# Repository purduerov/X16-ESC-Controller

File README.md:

# Readme for X16-ESC-Controller
This board turns signals from the Pi into PWM signals that go to the ESC Adapter

Whenever you make a new part, download the datasheet and save it here _**and**_ with the part in the parts library

Always pull other people's changes before beginning to work
`git pull`

Be sure to push your changes after  working on them. Run:
1. `git add .` to add any files in this directory or a subdirectory
or `git add -u` to add any modified files
2. (Optional) `git clean -nX` to see what ignored files can be removed
	`git clean -fX` removes ignored files (Eagle backups)
3. `git commit -m "helpful commit message"` with a description of the work that you did
4. `git push` to push your work to github

Other helpful commands
* `git status` says information about modified and staged files
* `git log` shows the recent commits of the repository
* `git log filename.extension` show the recent commits for just that file
* `git checkout first-couple-letter-of-commit-id` lets you go back to a previous version
* `git checkout master` brings you back to the latest commit
* `git tag` lists the tags
* `git tag -a orderX -m "the version of the board placed for the X'th order"` tag a specific commit
* `git push --tags` needed to push tags to remote
* `git show orderX` show the commit log for the given tag
* `git checkout orderX` go back and interact with the files at the tagged commit

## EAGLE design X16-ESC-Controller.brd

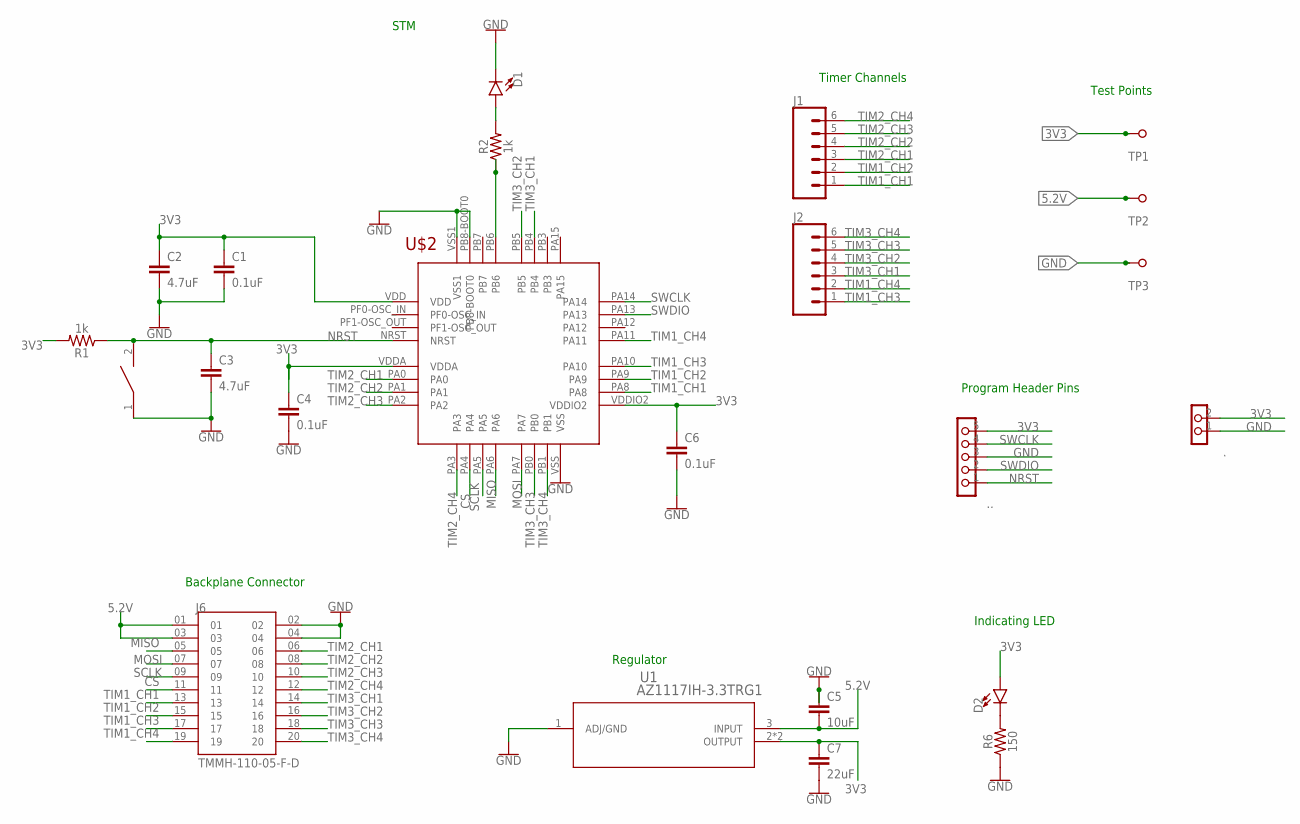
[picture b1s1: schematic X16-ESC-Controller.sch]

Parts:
.: TEST_PIN-1X2; 1X02
..: TEST_PIN-1X5; 1X05
C1, C4, C6: 0.1uF; 0603
C2, C3: 4.7uF; 0603
C5: 10uF; 0603
C7: 22uF; 0603
D1, D2: Green; LED-0805
J1, J2: CONN_06NO_SILK_NO_POP; 1X06_NO_SILK
J6: TMMH-110-05-F-D; SAMTEC_TMMH-110-05-F-D
R1, R2: 1k; 0603
R6: 150; 0603
TP1, TP2, TP3: TESTPOINT_5.04MM
U1: AZ1117IH-3.3TRG1; SOT223_AZ1117I_6P5X3P5_DIO
U$2: IC_STM32F042K6T6; STM32F042K6T6
U$3: SWITCH_DISCRETECOMPONENTS; DISCRETECOMPONENTS_SW_2512

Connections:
3V3: ..2, ...5, C1.1, C2.1, C4.1, C6.1, C7.1, D2.A, R1.2, TP1.TP, U1.2 (OUTPUT), U1.4 (OUTPUT), U$2.VDD, U$2.VDDA, U$2.VDDIO2
5.2V: C5.2, J6.01, J6.03, TP2.TP, U1.3 (INPUT)
CS: J6.11, U$2.PA4
GND: ..1, ...3, C1.2, C2.2, C3.2, C4.2, C5.1, C6.2, C7.2, D1.C, J6.02, J6.04, R6.1, TP3.TP, U1.1 (ADJ/GND), U$2.PB8-BOOT0, U$2.VSS, U$2.VSS1, U$3.1
MISO: J6.05, U$2.PA6
MOSI: J6.07, U$2.PA7
unnamed: D2.C, R6.2
unnamed: R2.1, U$2.PB6
unnamed: D1.A, R2.2
NRST: ...1, C3.1, R1.1, U$2.NRST, U$3.2
SCLK: J6.09, U$2.PA5
SWCLK: ...4, U$2.PA14
SWDIO: ...2, U$2.PA13
TIM1_CH1: J1.1, J6.13, U$2.PA8
TIM1_CH2: J1.2, J6.15, U$2.PA9
TIM1_CH3: J2.1, J6.17, U$2.PA10
TIM1_CH4: J2.2, J6.19, U$2.PA11
TIM2_CH1: J1.3, J6.06, U$2.PA0
TIM2_CH2: J1.4, J6.08, U$2.PA1
TIM2_CH3: J1.5, J6.10, U$2.PA2
TIM2_CH4: J1.6, J6.12, U$2.PA3
TIM3_CH1: J2.3, J6.14, U$2.PB4
TIM3_CH2: J2.4, J6.16, U$2.PB5
TIM3_CH3: J2.5, J6.18, U$2.PB0
TIM3_CH4: J2.6, J6.20, U$2.PB1

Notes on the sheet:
Timer Channels
Program Header Pins
Indicating LED
Regulator
Test Points
Backplane Connector
STM

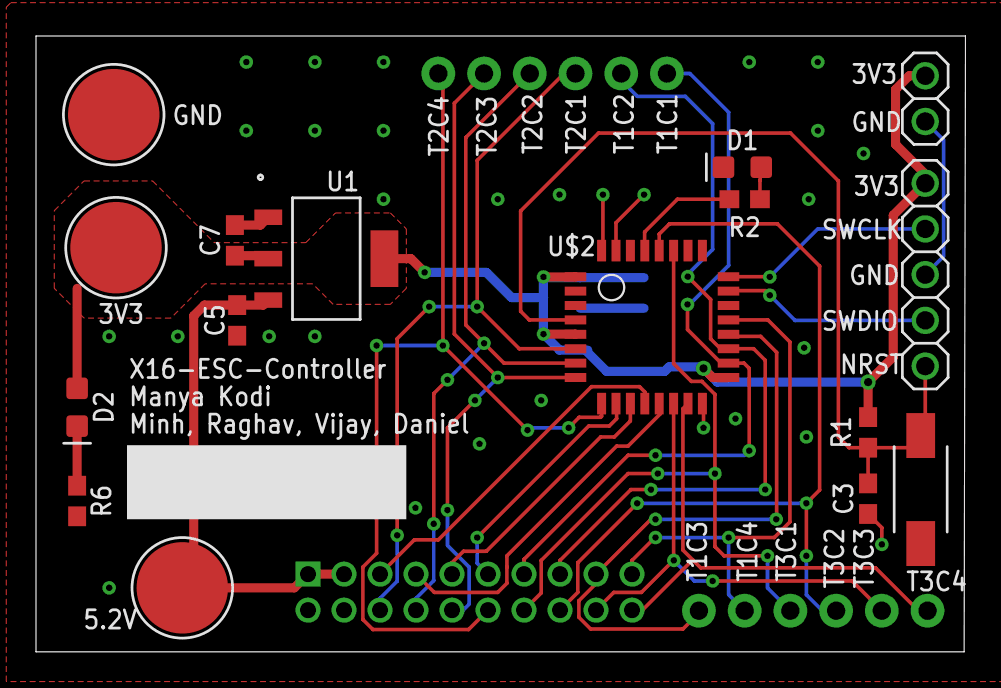
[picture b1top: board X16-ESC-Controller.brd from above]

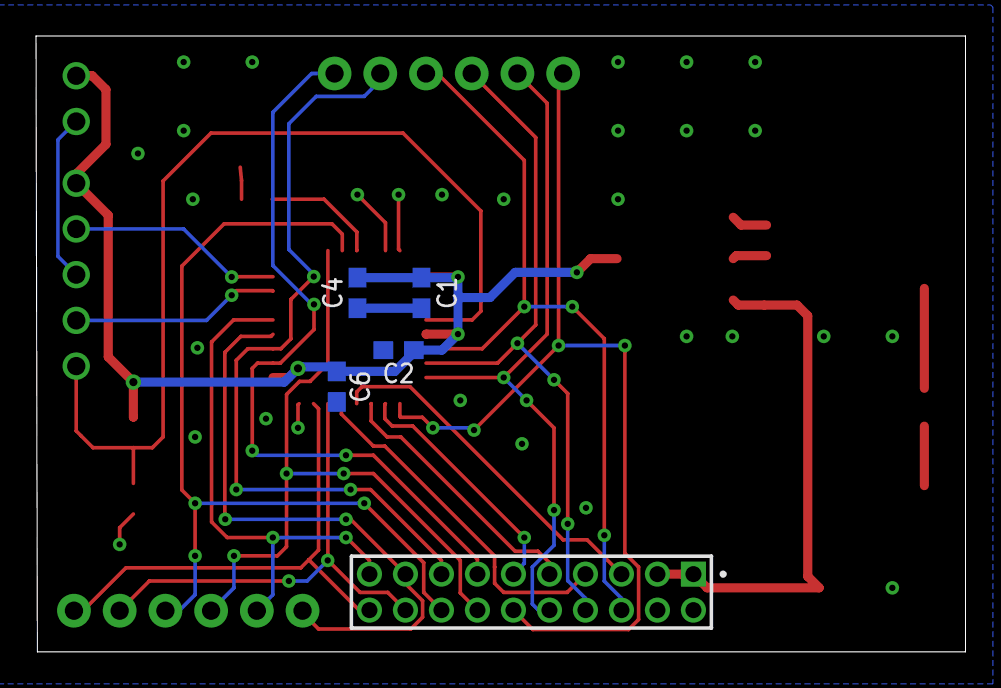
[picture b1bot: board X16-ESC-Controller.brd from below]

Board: 2 copper layers, 51.6 x 34.2 mm, 23 parts (5 on the bottom side), 25 nets.

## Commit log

2023-09-23 Init
2023-09-23 Added .gitignore file
2023-10-05 STM & Connectors
2023-10-18 schematic
2023-10-19 final?
2023-10-25 testing
2023-11-04 11/4/2023
2023-11-04 11/04/23
2023-11-09 11/08/23
2023-11-16 11/16/23
2023-11-18 11/17/23
2023-12-02 New programming header
2023-12-07 12/16/2023
2023-12-07 12/6/2023 pt2
2023-12-07 12/06/2023 pt3
2023-12-21 increased text size + minor changes to trace routing
2023-12-23 fixed LDO thermals and pad 4, updated LDO caps to datasheet recommended, cleaned up silkscreen
2023-12-29 Minh Update 1

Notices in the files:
parts and their libraries:
SparkFun-Capacitors: Licensing: Creative Commons ShareAlike 4.0 International - https://creativecommons.org/licenses/by-sa/4.0
COPYRIGHT: Copyright (C) 2023 Ultra Librarian. All rights reserved.
